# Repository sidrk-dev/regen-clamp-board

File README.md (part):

# Regen clamp + soft-start board (rev F)

**Quick links:** [JLCPCB Ordering & Settings](#ordering-and-cost) · [Manufacturing Files (`jlcpcb/`)](jlcpcb/) · [Schematic PDF](docs/regen_precharge_schematic.pdf) · [Factory Assembly View](docs/regen_precharge_revF_factory.png) · [Bring-up](#bring-up)

**Prototype for bench evaluation.** The board has not been built or measured. KiCad ERC and DRC pass on this copy,
and the control rail and braking figures below are design targets from calculation and simulation.

**Brake capacity.** The brake can absorb at most (supply + trip) ÷ R. With one 2 Ω resistor at 36 V and a +4 V trip
that is 20 A of current returned by the motors, net of what the other joints draw. Above that the bus keeps
rising: in simulation a 22 A, 15 ms return reaches 44.2 V, past the moteus r4's 44 V absolute maximum, and 27 A
reaches 53.8 V. Either limit the arm's deceleration and backdriving so the net returned current stays under
about 18 A at 36 V, or fit two resistors in parallel (see [Two brake resistors](#two-brake-resistors-in-parallel)).
Measure the returned current, resistor duty and connector fit before fast or backdriven operation. The
[engineering review](docs/arm-manufacturing-review.md) has the sweep, the assembly files checked and the
release gates.

A 125 × 100 mm two-layer board that sits between a bench supply and the arm.
The supply plugs into an XT60 in the middle of the left edge; five XT30
outputs sit along the right edge. Outputs 1–3 feed the arm's IM6014 motors, two or
three daisy-chained on each; output 4 feeds the gripper's moteus controller and
output 5 is a spare. It works from 24 V to 48 V supplies, with the brake threshold
set by RV1. A #8-32 mounting hole sits in each corner. It does two jobs:

1. **Regen clamp.** An ideal diode stops motor regeneration from flowing back
   into the supply. When braking pushes the motor bus a set amount above the
   supply, two MOSFETs dump the energy into an external brake resistor. A red
   LED stretches the brake indication by roughly 0.3 s under the simulated conditions.
2. **Soft start (precharge).** The output turns on at about 140 V/s, to reduce inrush when enabling a discharged output. It does not prevent
   sparks when connecting a load to an already charged output bus.

Design inspiration: the [ODrive Regen Clamp](https://docs.odriverobotics.com/v/latest/hardware/regen-clamp-datasheet.html)
(ideal diode plus a brake chopper whose threshold is relative to the input) and
the [mjbots mjpower-ss](https://github.com/mjbots/power_dist/tree/main/hw/mjpower-ss)
(a high-side FET ramped slowly to precharge the load, with an output on/off switch).

## Board renders

| Power input and brake connector | Motor outputs and brake connector |
| --- | --- |
|  |  |
| **Power-input side, opposite corner** | **Motor-output side, opposite corner** |
|  |  |

## Revisions

None of these has been ordered.

Rev F started as a cost-down of rev E. Later rev F edits adjusted the top-layer copper clearances described below.

- **Ordered in 1 oz copper instead of 2 oz.** JLC's live quote on 2026-11-11 for five 125 × 100 mm boards was
  $47.40 in 2 oz and $10.10 in 1 oz. A sheet-resistance and heat calculation from the board file
  (`review_tools/copper_check.py`, see Current handling) gives 3.1 mΩ and 2.2 W of copper heat at 27 A in 1 oz,
  against 1.5 mΩ and 1.1 W in 2 oz; the hottest spot, a MOSFET tab, is calculated at about 65 K above ambient in
  still air against 46 K. The layout still meets JLC's 2 oz rules, so the same Gerbers can be ordered in 2 oz
  if you want that margin back.
- **SW1 is hand-soldered**, which drops one extended-part fee ($3.07). The front stencil now omits its pads and the other hand-solder positions.
- **D12 is a BZT52C16** (C19077413, 15.2–16.8 V) instead of a BZT52C15, same SOD-123 footprint. JLC's catalogue data
  lists it as a Preferred part, with no loading fee on Economic assembly; JLC's part page only says Extended, so check the
  fee on the order page. The fault limit on the control rail rises from about 15 V to under 17 V, still below the
  20 V limits of U4 and the MOSFET gates.
- **Silkscreen:** connector outlines are trimmed 0.25 mm inside the board edge and the MOSFETs' small pin-1 dot is
  gone (Q9's sat on C13's pad; the heavy mark beside pin 1 stays). DRC now reports no warnings at any severity and
  the gate waives nothing. The project footprint library holds the same edits.
- **BUS_ADC** is the new name of the VBUS_ADC telemetry net. Konnect's design review took the old name for a power
  rail and asked for a 10 µF capacitor on it; it now reports no findings.
- The back legend reads rev F, 27 A max, 1 oz Cu, and has a line with the 36 V and 48 V settings.
- **From an independent review of the public rev E files (15 Nov 2026).** It found no netlist, pin, copper or
  fab-file error. Of its four layout points, two were already fixed here (SW1's direction, J5's slot pads) and two
  still held and are fixed now:
  - *Bus-voltage pads were 0.40 mm from ground copper*; IPC-2221B gives 0.5 mm for uncoated terminations at 51–100 V,
    which the bus reaches during braking on a 48 V supply. Every pad on a net that can pass 50 V is now at least
    0.5 mm from ground copper, and the hand-soldered bus pins of the XT connectors and electrolytics 1.0 mm.
    `review_tools/bus_clearance_check.py` shows 29 pads under 0.5 mm before and none after. Raising the whole top
    ground pour to 0.5 mm was tried first and rejected: it cut the ground of U4 and C19.
  - *The back legend ended 0.08 mm from the board edge*; it is moved 5 mm right. KiCad's DRC only reports
    silkscreen that crosses the edge, so `review_tools/silk_edge_check.py` now checks the margin.
  - *48 V margin*: the limit at 48 V is now +5 V (TP9 at most 7.7 V) instead of +6 V, as the review recommends (this also keeps `U3A`'s inputs below the `LM393` cold `VCC − 2.0 V` common-mode ceiling up to 55 V).
  - `tools/review_tools/check_bom.py` now checks capacitor voltage ratings, electrolytic can dimensions, and `>= 75 V` (`>= 150 V` on `R6, R36`) working-voltage ratings on bus-connected resistors against the catalogue.
  - *0.1 % sense resistors*, added 16 Nov because the board will also run on 48 V: R10 and R14 are now 100 k 0.1 %
    (Yageo RT0603BRD07100KL, C122538) and R11 and R15 20 k 0.1 % (RT0603BRD0720KL, C723637), same 0603 footprint,
    75 V rated. The review puts the trip spread at 48 V at about 0.6 V with them, against 3.5 V with 1 % parts, so the
    brake releases above the supply in every corner and the interlock is a backup. Both values remain on the
    machine BOM as Extended parts. The tolerance figures elsewhere in this file (±1.4 V at 36 V, ±1.8 V at 48 V) are the
    older 1 % numbers and are now pessimistic. `build-scripts/sense_resistors.py` is the record.
  `build-scripts/review_nov15.py` is the record of the board edits.
- **SW1 is labelled OFF and ON at the two ends of its travel**, in place of one "ON/OFF" caption. The MSK12C02
  drawing shows the knob at the pin-3 end joining pins 3 and 2, and at the pin-1 end joining 2 and 1. Pin 1 is ground
  and pin 2 is EN, so ON is the slider toward the bottom board edge. `tools/check_parts.py` now fails if the labels are swapped.
- **Connector polarity settled from the Amass drawings**, and checked by `tools/check_parts.py`: pad 2 of J1 and of
  J2–J4, J6, J7 is the contact at the flat end of the housing, which is the + contact (see Verification status).
- New simulations: `sim_post_layout.cir`, `sim_soft_start.cir`, and `tools/review_tools/full_board_spice_check.py` (see Verification status).
- **The six TO-263 MOSFETs (`Q1, Q2, Q3, Q7, Q8, Q9`) stay on JLCPCB's SMT reflow line**, while the 1206 capacitors
  (`C1, C2, C6`) remain hand-soldered (reflow them with hot air or a hot plate rather than a point iron,
  to avoid ceramic thermal-shock cracks). The MOSFETs retain the corrected 3D model offset and front stencil paste openings.
- **R6, the SMC and SMA diodes (D1, D2, D4, D7), the two SOD-123 Zeners (D11, D12) and the SOT-223 transistor
  (Q4) stay machine-placed.** An earlier commit on this branch moved them to hand soldering; only D11 carried a fee,
  so the other seven added hand work for no saving, and the owner asked for them to go back on the machine.
  The schematic's assembly field and the PCB placement exclusions drive the exports.
- **From a follow-up review (17–18 Nov 2026):** `J1` and `J5` contact holes are centred in Amass's `2.90 +0.10/-0.00 mm`
  and `0.80 +0.10/-0.00 × 1.90 +0.10/-0.00 mm` windows at **3.0 mm** with **0.9 × 2.0 mm** fixing slots (`1.5 × 2.6 mm`
  pads, keeping the `0.30 mm` plated ring) so JLCPCB's `-0.08 mm` plating tolerance cannot finish undersize; thermal relief
  spokes now protect the five 470 µF bulk capacitors (`C7, C8, C15, C16, C17`), `J12` pin 1, the hand-soldered SMDs
  (`C1, C2, C6, SW1`), and 58 small `0603`/`0805`/`SOD` passives (preventing reflow tombstoning and `SW1` housing heat
  damage while keeping MOSFET, power-diode, and XT connector pads solid); `C8`'s silkscreen label moved clear of `D2`'s
  body; `tools/sch_layout.py` is bundled in `tools/`; `B.Paste` is included in the 11-file Gerber archive; and the schematic
  title block and notes are updated to rev F, 27 A, four output bulk capacitors and D12 under 17 V (`tools/rev_f_review_fixes.py`).
- The PCB and schematic both use the bundled 1 mm fiducial footprint so that a change in the installed KiCad library does not affect the release checks.
- `build-scripts/cost_down.py` and `tools/rev_f_review_fixes.py` are the record of these edits.

Rev E, changes from rev D. Most of these were found by independent reviews:

- **U2 CJ431 pins corrected.** The board used TL431 numbering, but this part's SOT-23
  is pin 1 REF, pin 2 K, pin 3 A. The control rail could not have worked.
- **RV1 ends swapped**, so clockwise raises the brake threshold.
- **J1 and J5 holes enlarged** to 2.9 mm with 0.8 × 1.9 mm fixing slots, per the
  XT60PW-M30 drawing served for C98732. The old 2.7 mm holes and 0.6 × 1.7 mm slots
  could not take the connector. The XT60PW-F PDF gives no PCB holes, so J5 uses the
  same sizes.
- **C13 moved out from under Q9, and R30–R33 moved clear of the MOSFET plastic.**
  C13 sat under Q9's body and gate lead, which would have stopped assembly. A DRC
  warning showed it, and it had been wrongly waived as cosmetic.
- **Ideas from a friend's board:** a UCC27517 gate driver (U4) replaces the Q5/Q6 transistor pair, so
  the brake switches in tens of nanoseconds and the LM393 no longer sinks a transistor's base current;
  the five 470 µF capacitors (four on the output, one on the input) are now 100 V (12.5 × 30 mm, same footprint, 5 mm taller); and J12 gives a
  microcontroller GND, BUS_ADC (VOUT × 0.053, 3.3 V at 62 V) and BRK_FLAG (open drain, low while braking).
- **Q4 is now a BCP56-16 in SOT-223** (94 °C/W, 1.33 W) instead of an MMBT5551 in SOT-23 (416 °C/W).
  Braking adds rail load, and the old part could pass 150 °C at moderate ambient. It sits at the lower left.
- **J5's fixing pads give a 0.3 mm plated ring** on every side, for JLC's 2 oz rule; J5 moved 0.4 mm inboard.
- **Copper kept out of an 11.5 mm circle round each corner hole**, both layers, so a
  metal screw head or washer can't short VIN or VOUT to a grounded standoff.
- **D10 (1N4148WS) added across Q4's base and emitter.** When VOUT collapses while C9
  still holds the rail up, the junction no longer breaks down in reverse.
- **D11 (BZT52C12, 12 V) clamps HGATE to VOUT.** The 400 nF soft-start capacitor holds
  HGATE up when VOUT falls, and with no clamp HGATE minus OUT could pass U1's 15 V
  absolute maximum and the MOSFETs' 20 V gate limit: 18 V or more after long regen, far
  more on a supply removal or output short. R5 limits the peak clamp current to ~47–60 mA (`< 0.3 mJ`).
  Scope HGATE minus OUT at bring-up.
- **D12 (BZT52C15) clamps Q4's base.** If U2 or R7 opens, R6 would pull the rail up to the bus,
  past the LM393's 36 V and the brake MOSFETs' 20 V gate limit. Now the rail stays under about 15 V.
- **Five XT30 outputs instead of three**, so the arm's seven motors split two or three per
  output, all within the XT30's 15 A rating.
- **C3 raised to 470 nF**, from TI's VCAP ≥ 10 × (Ciss Q1 + Ciss Q2) with four MOSFETs.
- **C17 (470 µF 100 V) added on VIN.** Only 1 µF sat there, so turning Q2/Q8 off under load
  could spike VIN past U1's 70 V through the supply lead's inductance. Connect the supply with it off.
- **J2–J5 moved out** so each connector's nose hangs off the board edge. The mating plug's
  shell wraps the nose and could have hit the PCB and stopped short of full mating.
- **D1 and D2 ground returns strengthened** from one via to three.
- **U1's exposed pad paste reduced to about 82 %** (0.08 mm smaller each side), per TI's stencil example.
- **From the final three-model review:** R40 (100 k) limits current into U3 pin 6 if the rail drops
  while C12 is charged; R41 (10 k) in Q10's base limits a reversed-supply fault path through Q10/Q11;
  C18 (1 nF) filters noise from the J11 wiring on CMP_OUT; C19 (1 µF) is a local supply for the
  brake gate driver (Q5/Q6 then, U4 now); C3 is now 1 µF so it stays above TI's 271 nF after DC-bias loss; C13 moved
  0.4 mm further from Q9's gate pad; connector fixing pads enlarged for 2 oz plating; the screw
  keep-out widened so no copper sits within 5.5 mm of a hole centre.

Rev D, changes from rev C:

- XT60 input centred on the left edge and the three XT30 outputs centred on the
  right edge, so the four corners are free for #8-32 holes (4.5 mm, 5 mm in from
  each edge).
- Two debug LEDs: D8 (white, SUPPLY) shows the PSU is connected even with SW1
  off; D9 (yellow, THERM OPEN) shows, while the output bus is up, that the J11
  thermal loop is open, which is the usual reason the brake never fires.
- Eight more test points (TP18–TP25): OV, CDVDT, interlock, second brake gate,
  thermal loop, driver output, and two more GND holes by the input and outputs.
- The VIN pour now fills the area beside U1, which keeps input current density
  down with the XT60 in its new place.
- Design rules raised to JLCPCB's 2-layer 2 oz limits, 0.16 mm track and
  clearance (earlier revisions used 1 oz limits, 0.127/0.15 mm, and 51 tracks
  were too thin for 2 oz). The 2 oz stackup is now recorded in the board file.
- Three fiducials added, and the router's dead-end stubs removed.

Rev C, changes from rev B:

- XT60 input instead of XT90, and 3 outputs instead of 7.
- Brake interlock (Q10, Q11): the brake is intended to be held off while the ideal diode
  conducts. The behavioral latch test covers one tolerance corner; it does not
  prove that every transient and component fault avoids supply-fed braking. In rev B, worst-case
  1 % resistor tolerances at the lowest trim setting could put the brake's
  release point below the supply at 36–48 V, and the brake would then latch on
  and pass about 24 A from the PSU into the resistor.
- One 10 Ω gate resistor per paralleled MOSFET (R30–R33), to stop parasitic
  oscillation while the soft-start pair runs in its linear region.
- Gate drive nets run on the top layer between the power pours, so no gate
  traces cut the bottom ground plane.
- R26 470 Ω (was 1 kΩ): the intended emitter follower has more collector headroom. The
  earlier claim of a guaranteed 11.3 V rail at 15 V is withdrawn; CJ431 bias
  current and the exact U2 pinout must be corrected.
- TVS diodes D1/D2 use JLC's Preferred SMCJ51A (C42371549): same part, no
  extended-part fee.

## Ratings

These are board design targets. Each attached controller must tolerate the maximum
bus voltage, including regen and transients. Unitree's public N6014B-12.6 page
lists 24–75 V input, so 15 V is outside that motor's published range. Moteus
limits depend on the exact model: r4 is 44 V absolute maximum, c1 is 51 V,
and n1/x1 are 54 V. A generic "moteus" output is not validated for 48 V plus regen.
See the manufacturer [Unitree specification](https://www.unitree.com/IM6014/)
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
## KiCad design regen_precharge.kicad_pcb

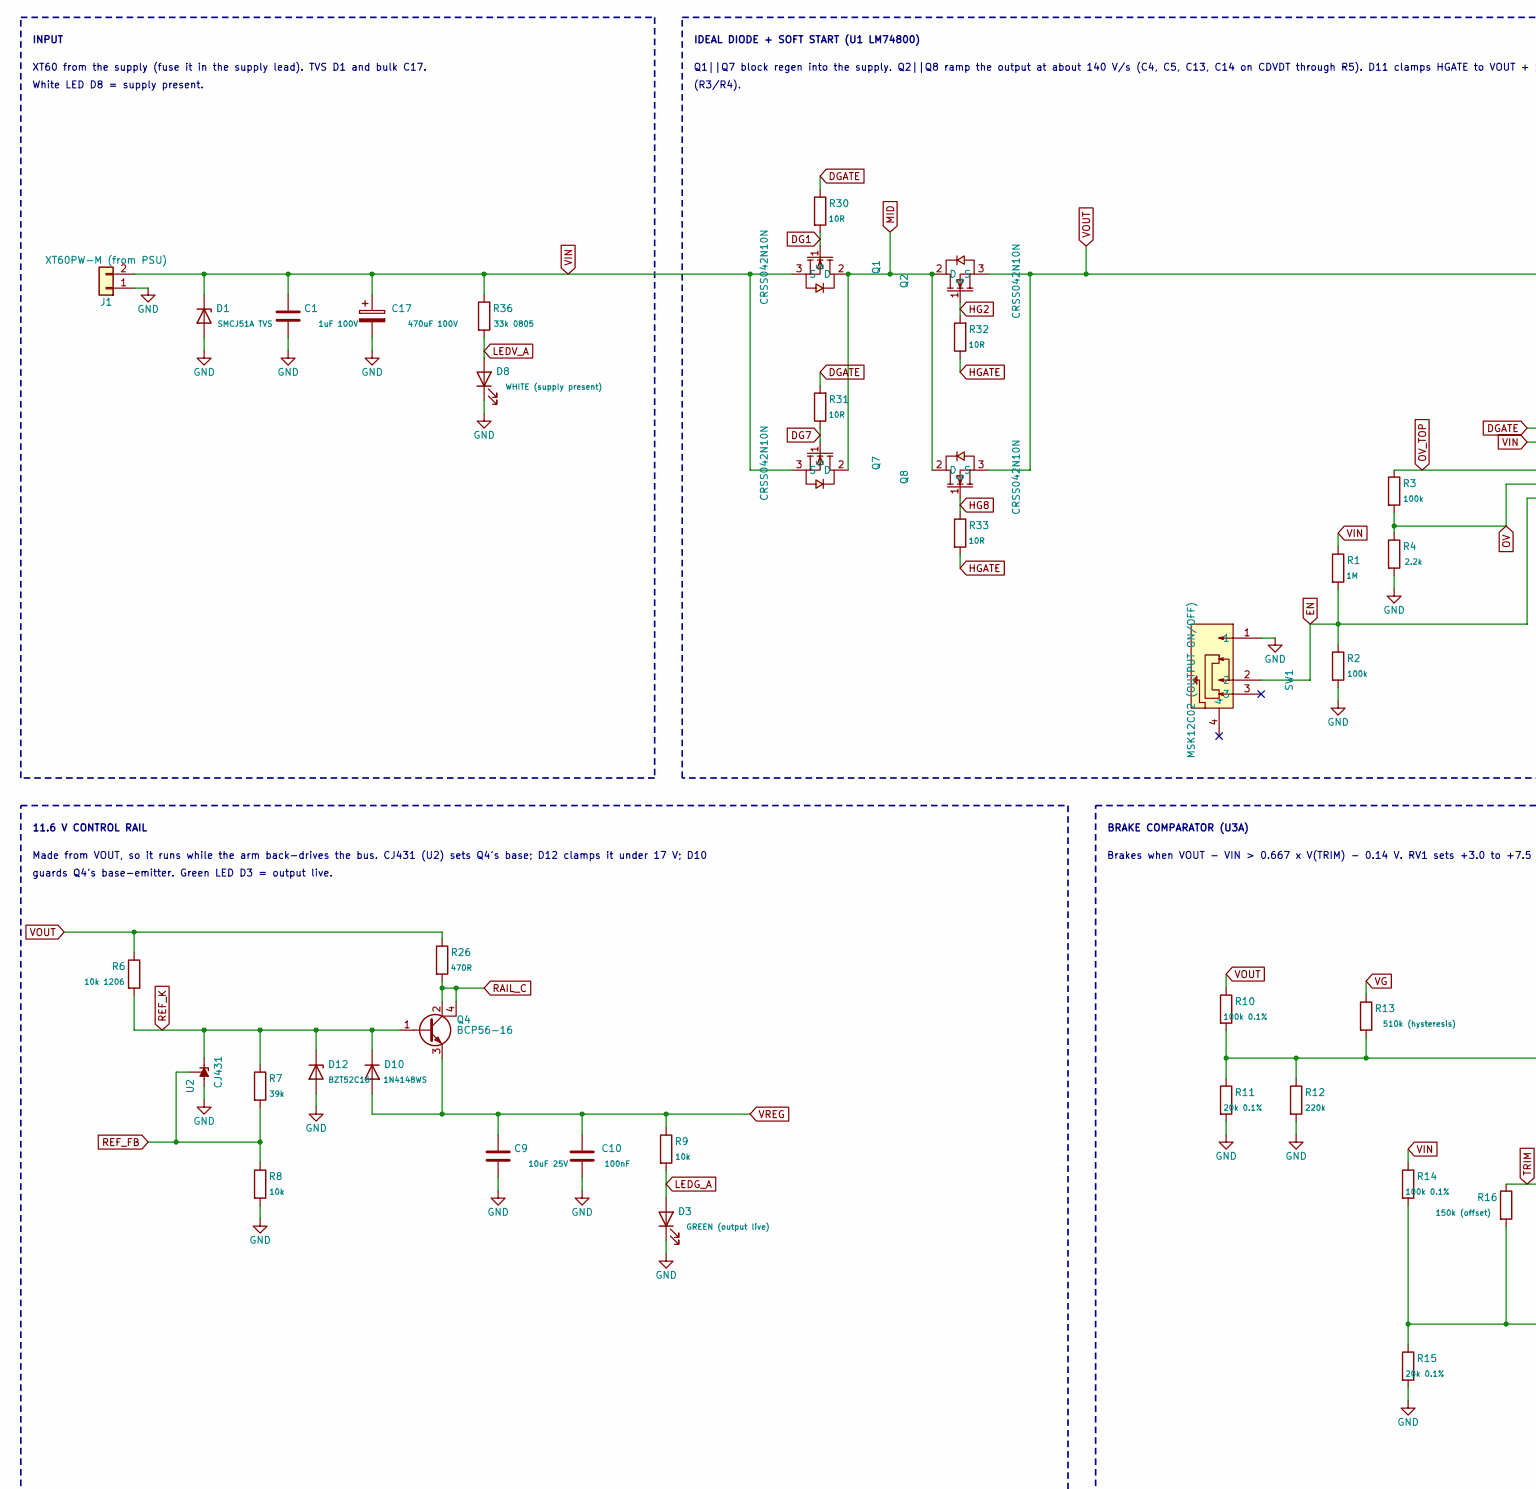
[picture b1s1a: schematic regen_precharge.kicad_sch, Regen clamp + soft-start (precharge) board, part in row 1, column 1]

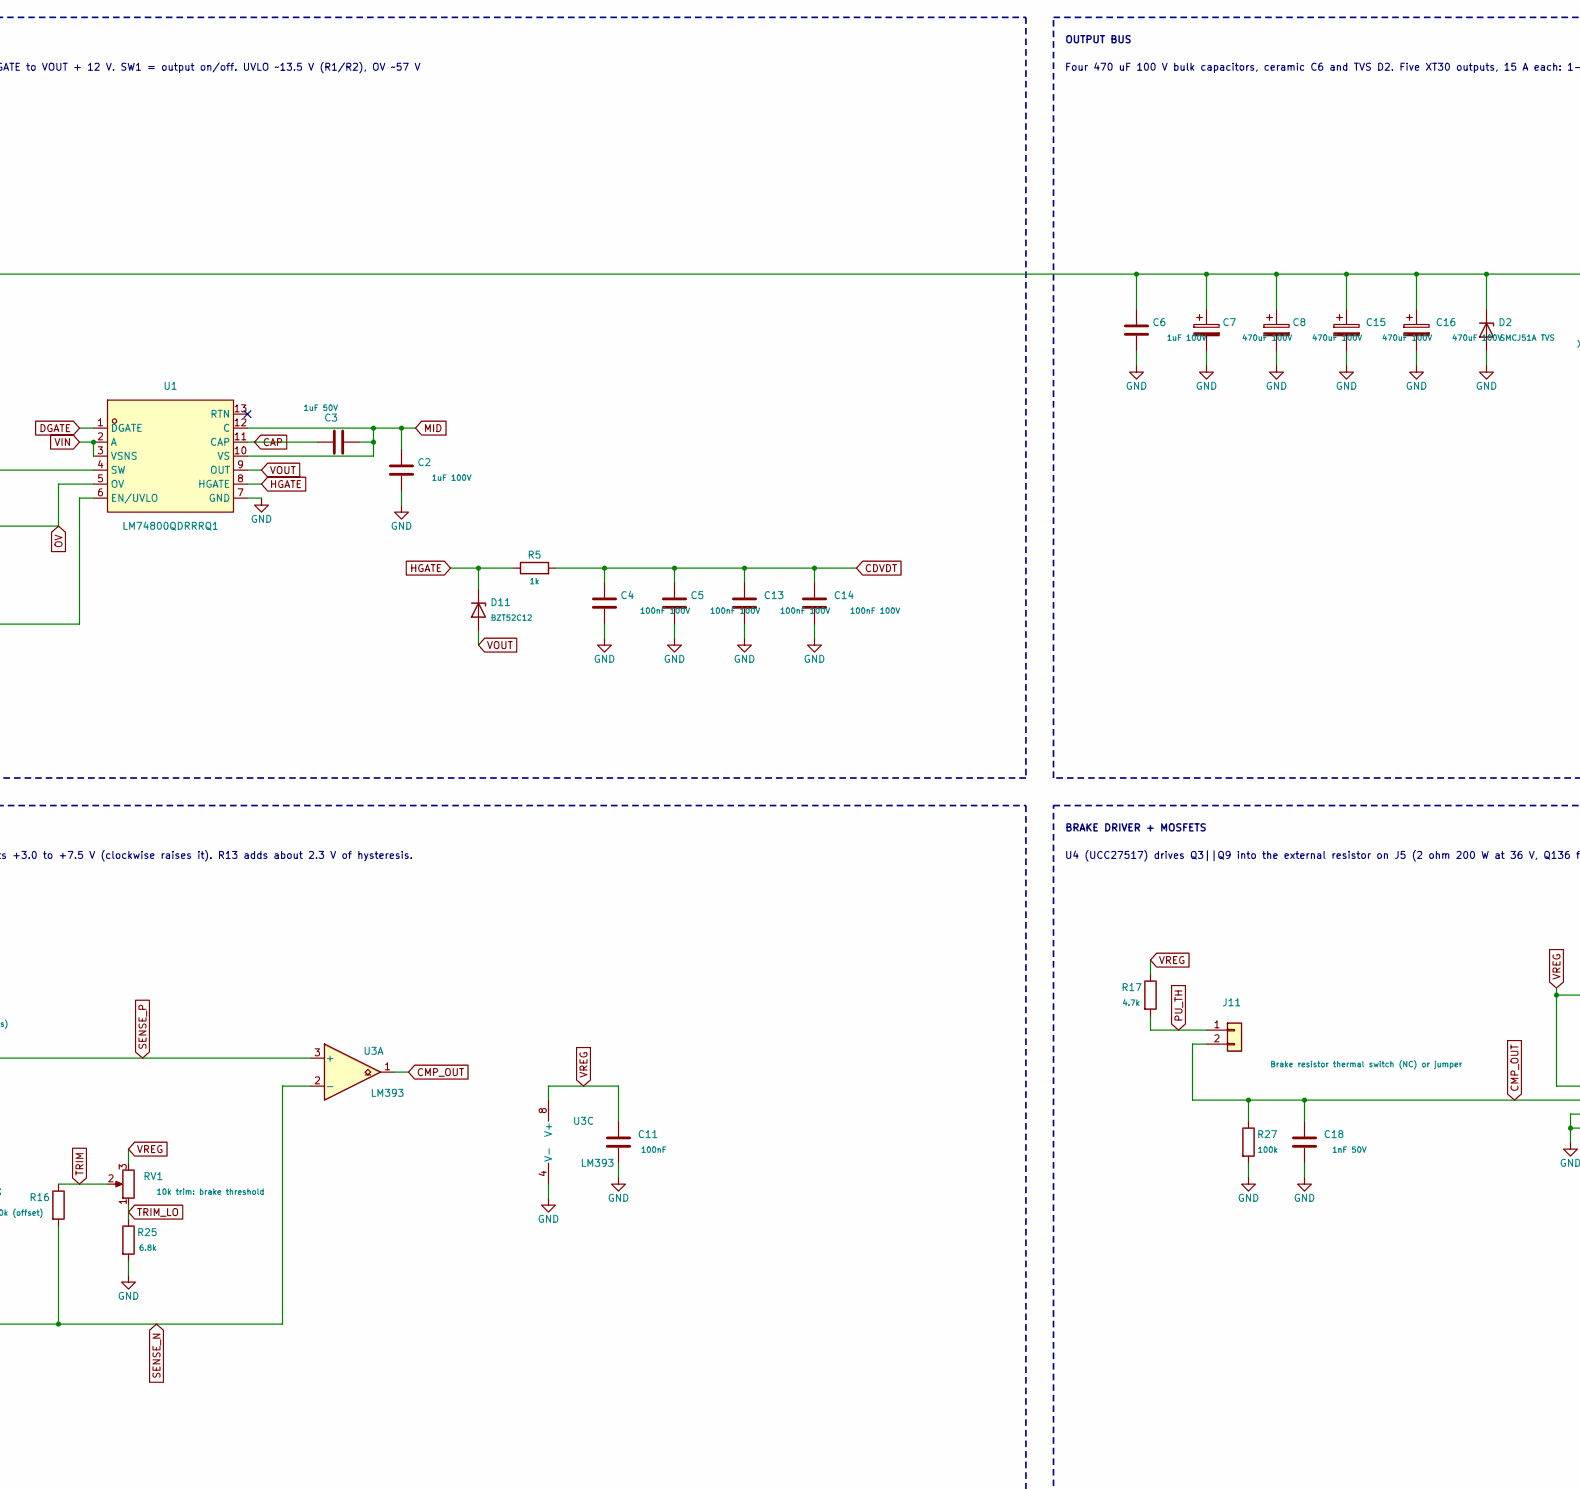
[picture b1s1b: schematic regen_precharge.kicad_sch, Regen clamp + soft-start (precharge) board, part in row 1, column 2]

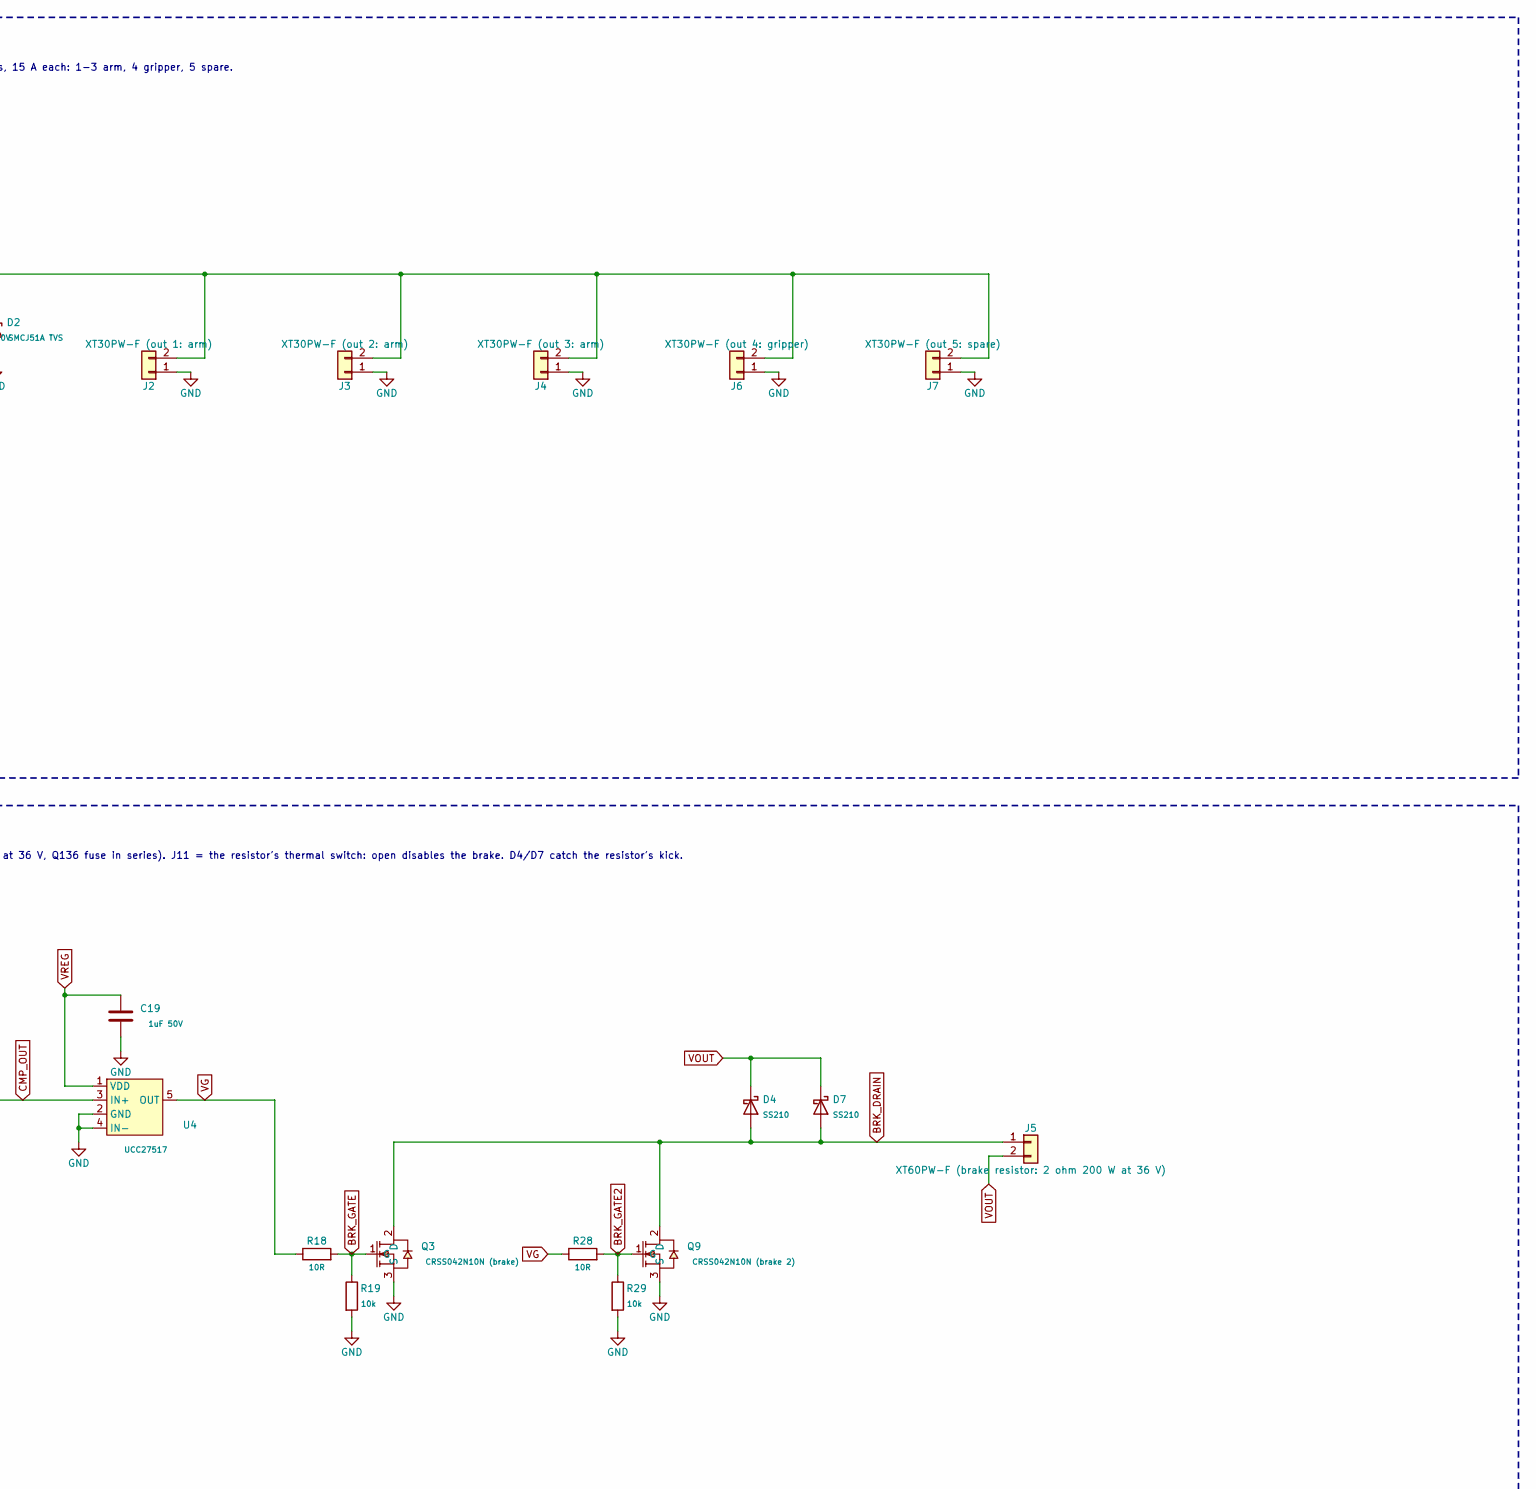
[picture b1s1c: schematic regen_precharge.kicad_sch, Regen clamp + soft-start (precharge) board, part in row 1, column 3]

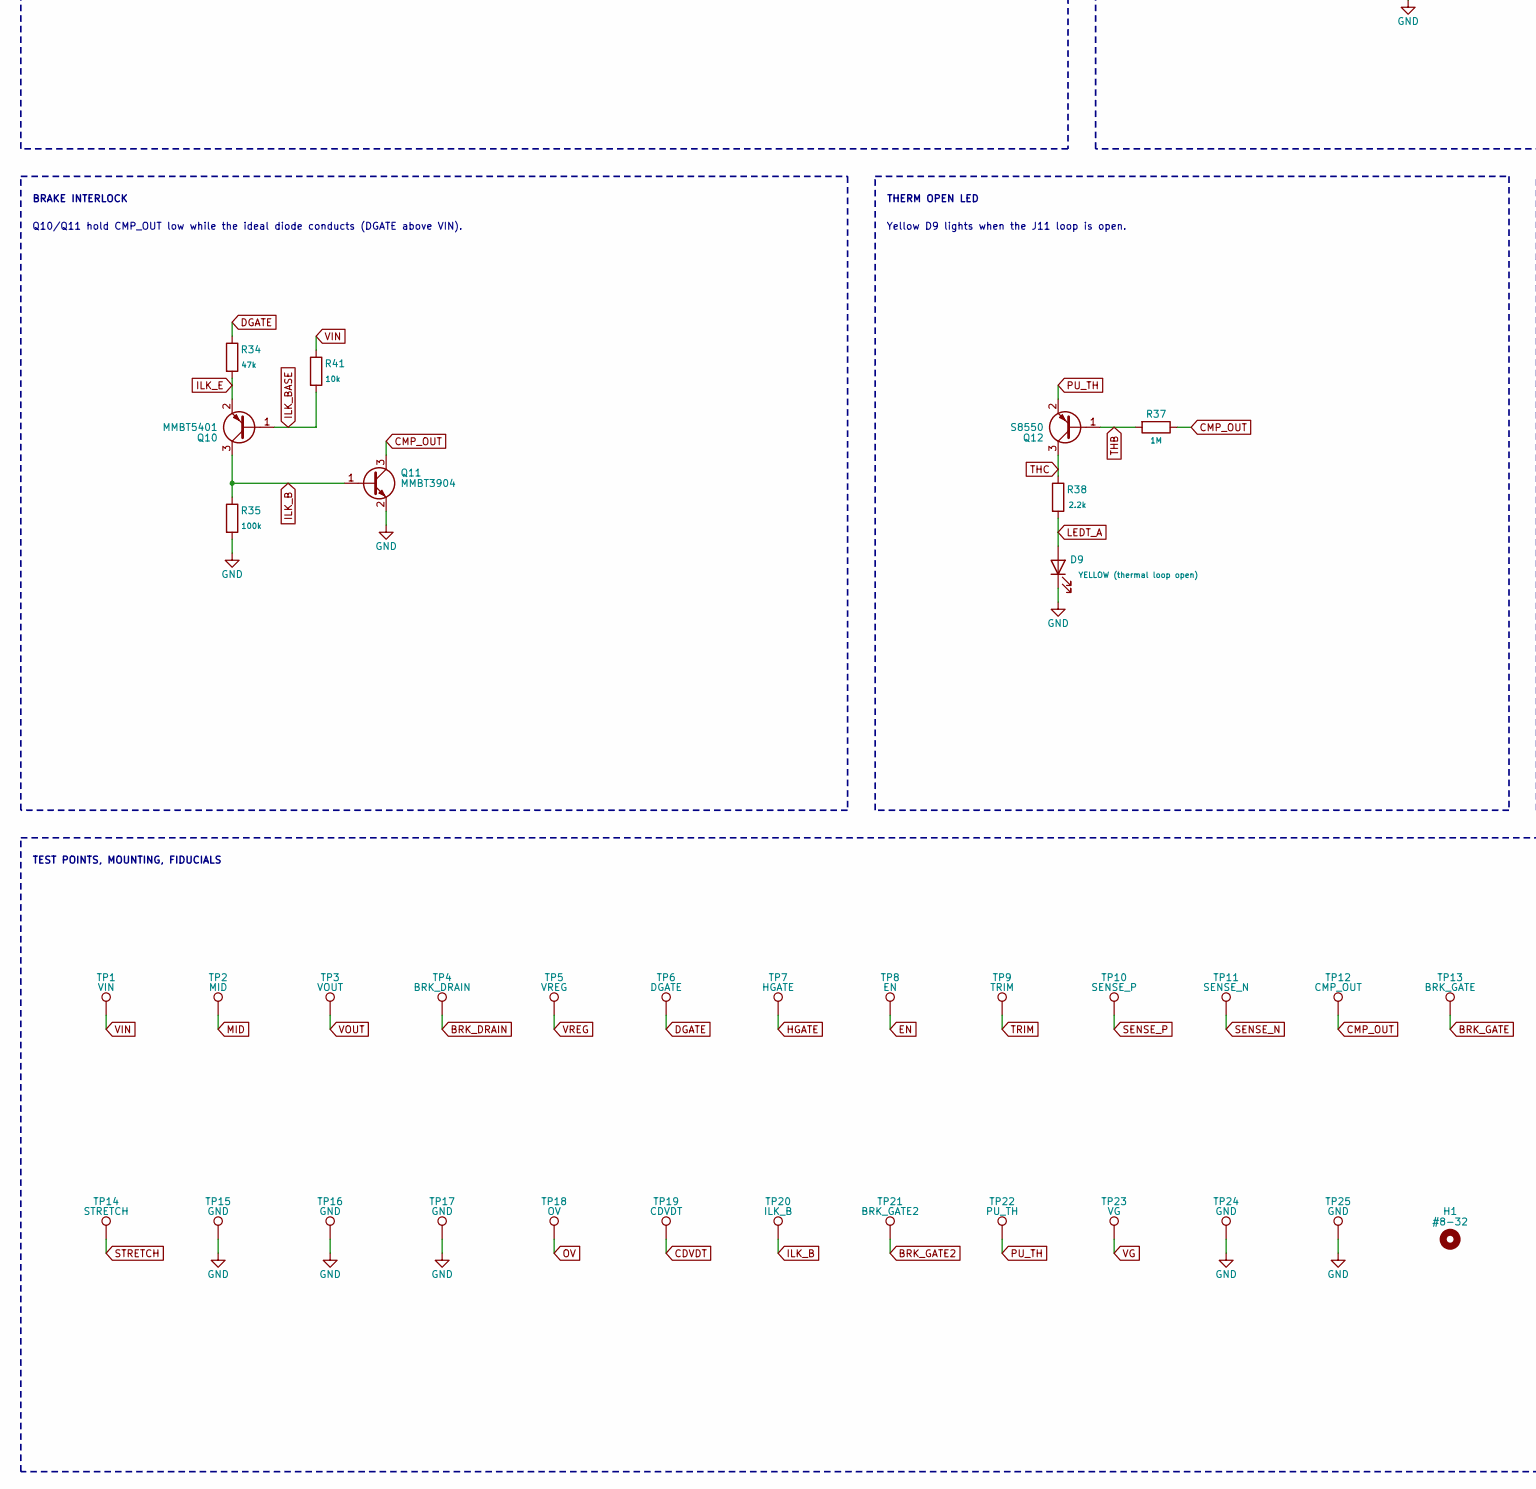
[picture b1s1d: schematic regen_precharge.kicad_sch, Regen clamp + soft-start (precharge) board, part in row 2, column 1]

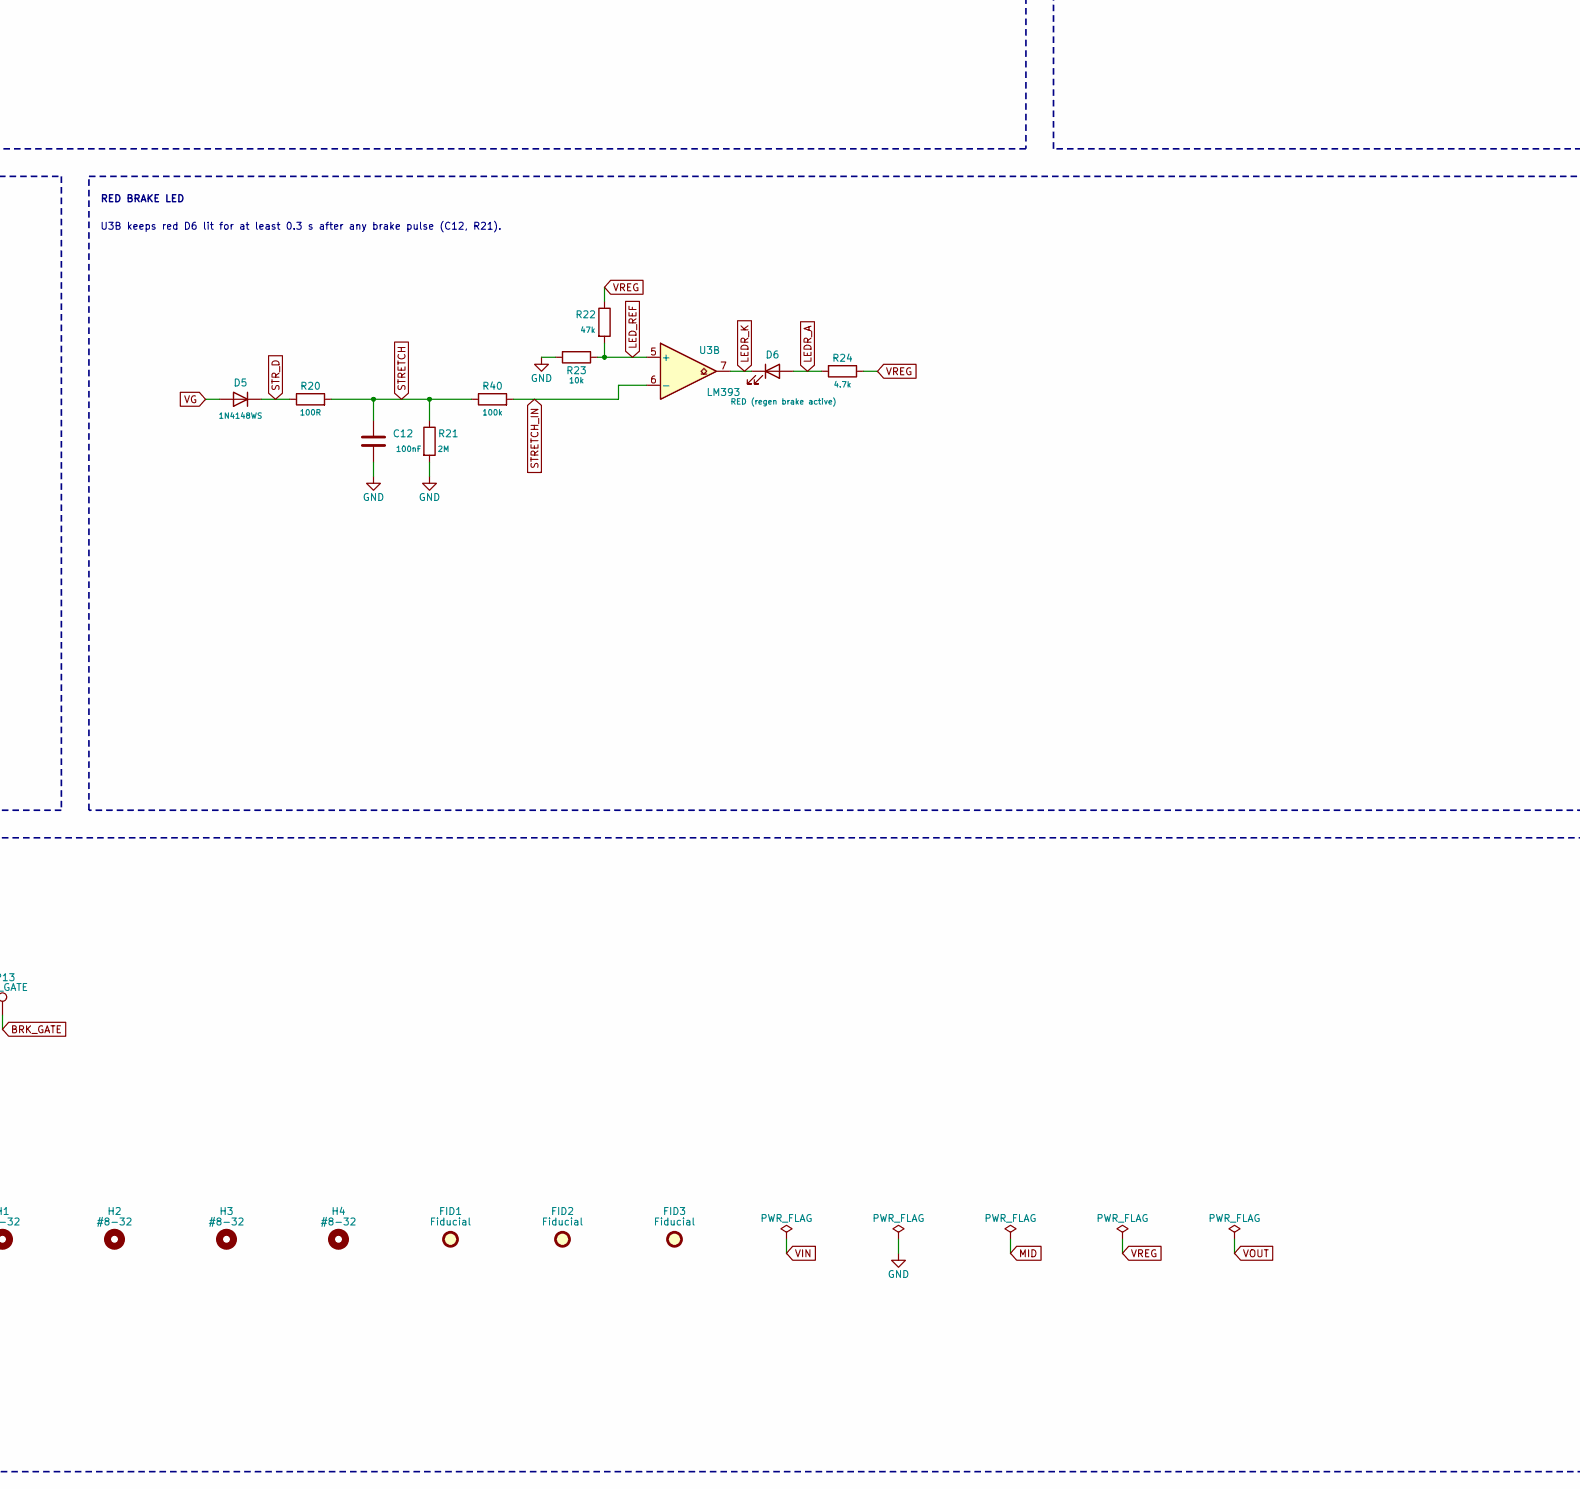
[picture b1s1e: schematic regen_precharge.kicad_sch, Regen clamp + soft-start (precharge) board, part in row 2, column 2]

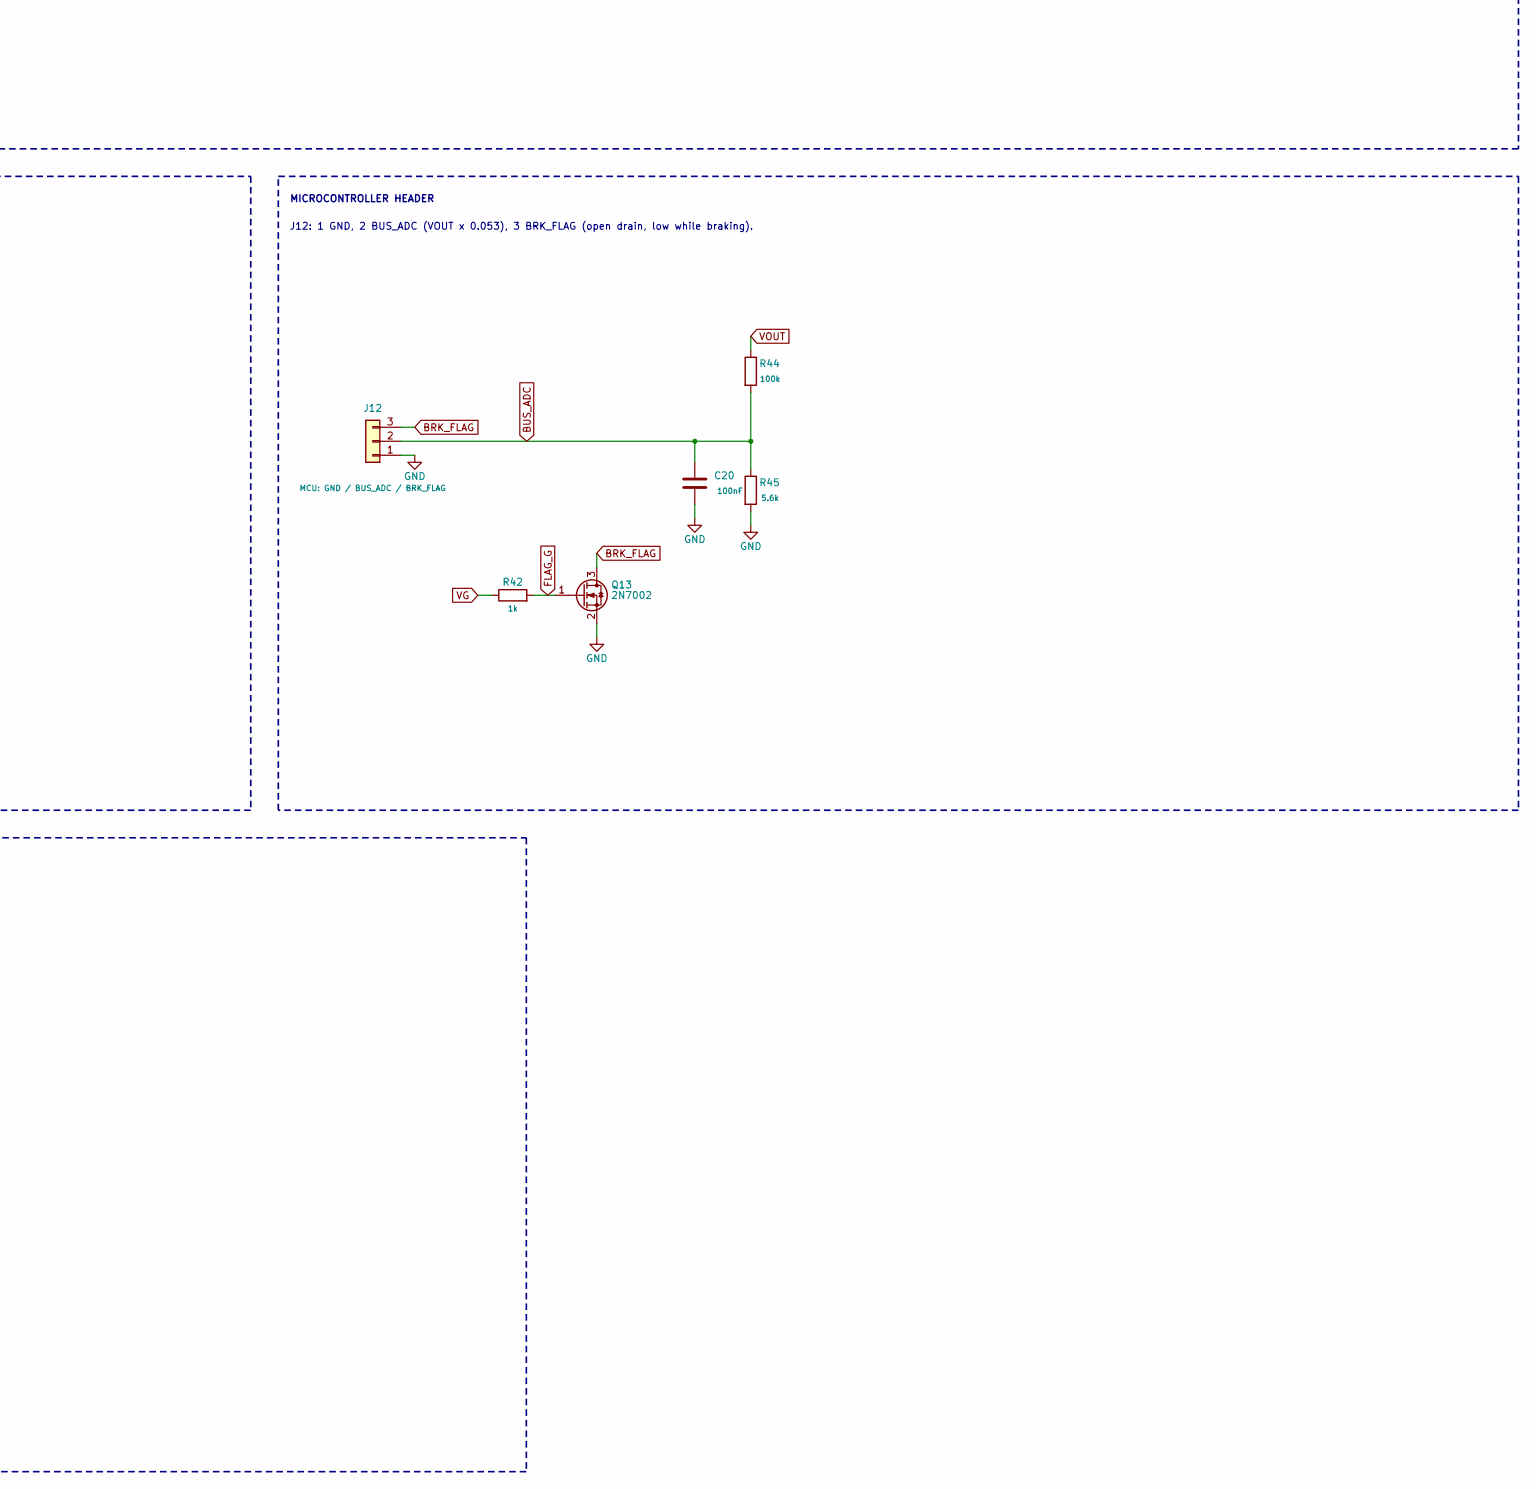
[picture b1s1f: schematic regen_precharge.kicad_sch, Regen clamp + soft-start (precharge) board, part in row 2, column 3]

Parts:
C1, C2, C6: 1uF 100V; C_1206_3216Metric; LCSC C13832
C3, C19: 1uF 50V; C_0603_1608Metric; LCSC C15849
C4, C5, C13, C14: 100nF 100V; C_0805_2012Metric; LCSC C28233
C7, C8, C15, C16, C17: 470uF 100V; CP_Radial_D12.5mm_P5.00mm; LCSC C443159
C9: 10uF 25V; C_0805_2012Metric; LCSC C15850
C10, C11, C12, C20: 100nF; C_0603_1608Metric; LCSC C14663
C18: 1nF 50V; C_0603_1608Metric; LCSC C1588
D1, D2: SMCJ51A TVS; D_SMC; LCSC C42371549
D3: GREEN (output live); LED_0805_2012Metric; LCSC C2297
D4, D7: SS210; D_SMA; LCSC C14996
D5, D10: 1N4148WS; D_SOD-323; LCSC C2128
D6: RED (regen brake active); LED_0603_1608Metric; LCSC C2286
D8: WHITE (supply present); LED_0603_1608Metric; LCSC C2290
D9: YELLOW (thermal loop open); LED_0805_2012Metric; LCSC C2296
D11: BZT52C12; D_SOD-123; LCSC C2932744
D12: BZT52C16; D_SOD-123; LCSC C19077413
FID1, FID2, FID3: Fiducial; Fiducial_1mm_Mask2mm
H1, H2, H3, H4: #8-32; MountingHole_4.5mm
J1: XT60PW-M (from PSU); AMASS_XT60PW-M30_1x02_P7.20mm_Horizontal; LCSC C98732
J2: XT30PW-F (out 1: arm); AMASS_XT30PW-F_1x02_P2.50mm_Horizontal_pegs; LCSC C2913282
J3: XT30PW-F (out 2: arm); AMASS_XT30PW-F_1x02_P2.50mm_Horizontal_pegs; LCSC C2913282
J4: XT30PW-F (out 3: arm); AMASS_XT30PW-F_1x02_P2.50mm_Horizontal_pegs; LCSC C2913282
J5: XT60PW-F (brake resistor: 2 ohm 200 W at 36 V); AMASS_XT60PW-F_1x02_P7.20mm_Horizontal_2.9mm; LCSC C428722
J6: XT30PW-F (out 4: gripper); AMASS_XT30PW-F_1x02_P2.50mm_Horizontal_pegs; LCSC C2913282
J7: XT30PW-F (out 5: spare); AMASS_XT30PW-F_1x02_P2.50mm_Horizontal_pegs; LCSC C2913282
J11: Brake resistor thermal switch (NC) or jumper; PinHeader_1x02_P2.54mm_Vertical; LCSC C492401
J12: MCU: GND / BUS_ADC / BRK_FLAG; PinHeader_1x03_P2.54mm_Vertical; LCSC C2937625
Q1, Q2, Q7, Q8: CRSS042N10N; TO-263-3_L10.2-W10.7-P5.08-LS16.2-TL; LCSC C410926
Q3: CRSS042N10N (brake); TO-263-3_L10.2-W10.7-P5.08-LS16.2-TL; LCSC C410926
Q4: BCP56-16; SOT-223; LCSC C41375109
Q9: CRSS042N10N (brake 2); TO-263-3_L10.2-W10.7-P5.08-LS16.2-TL; LCSC C410926
Q10: MMBT5401; SOT-23; LCSC C8326
Q11: MMBT3904; SOT-23; LCSC C20526
Q12: S8550; SOT-23; LCSC C105432
Q13: 2N7002; SOT-23; LCSC C8545
R1, R37: 1M; R_0603_1608Metric; LCSC C22935
R2, R3, R27, R35, R40, R44: 100k; R_0603_1608Metric; LCSC C25803
R4, R38: 2.2k; R_0603_1608Metric; LCSC C4190
R5, R42: 1k; R_0603_1608Metric; LCSC C21190
R6: 10k 1206; R_1206_3216Metric; LCSC C17902
R7: 39k; R_0603_1608Metric; LCSC C23153
R8, R9, R19, R23, R29, R41: 10k; R_0603_1608Metric; LCSC C25804
R10, R14: 100k 0.1%; R_0603_1608Metric; LCSC C122538
R11, R15: 20k 0.1%; R_0603_1608Metric; LCSC C723637
R12: 220k; R_0603_1608Metric; LCSC C22961
R13: 510k (hysteresis); R_0603_1608Metric; LCSC C23192
R16: 150k (offset); R_0603_1608Metric; LCSC C22807
R17, R24: 4.7k; R_0603_1608Metric; LCSC C23162
R18, R28, R30, R31, R32, R33: 10R; R_0603_1608Metric; LCSC C22859
R20: 100R; R_0603_1608Metric; LCSC C22775
R21: 2M; R_0603_1608Metric; LCSC C22976
R22, R34: 47k; R_0603_1608Metric; LCSC C25819
R25: 6.8k; R_0603_1608Metric; LCSC C23212
R26: 470R; R_0603_1608Metric; LCSC C23179
R36: 33k 0805; R_0805_2012Metric; LCSC C17633
R45: 5.6k; R_0603_1608Metric; LCSC C23189
RV1: 10k trim: brake threshold; RES-ADJ-TH_3362P; LCSC C58159
SW1: MSK12C02 (OUTPUT ON/OFF); SW-TH_MSK12C02; LCSC C431540
TP1: VIN; TestPoint_Pad_D1.5mm
TP2: MID; TestPoint_Pad_D1.5mm
TP3: VOUT; TestPoint_Pad_D1.5mm
TP4: BRK_DRAIN; TestPoint_Pad_D1.5mm
TP5: VREG; TestPoint_Pad_D1.5mm
TP6: DGATE; TestPoint_Pad_D1.5mm
TP7: HGATE; TestPoint_Pad_D1.5mm
TP8: EN; TestPoint_Pad_D1.5mm
TP9: TRIM; TestPoint_Pad_D1.5mm
TP10: SENSE_P; TestPoint_Pad_D1.5mm
TP11: SENSE_N; TestPoint_Pad_D1.5mm
TP12: CMP_OUT; TestPoint_Pad_D1.5mm
TP13: BRK_GATE; TestPoint_Pad_D1.5mm
TP14: STRETCH; TestPoint_Pad_D1.5mm
TP15, TP16, TP17, TP24, TP25: GND; TestPoint_THTPad_D2.0mm_Drill1.0mm
TP18: OV; TestPoint_Pad_D1.5mm
TP19: CDVDT; TestPoint_Pad_D1.5mm
TP20: ILK_B; TestPoint_Pad_D1.5mm
TP21: BRK_GATE2; TestPoint_Pad_D1.5mm
TP22: PU_TH; TestPoint_Pad_D1.5mm
TP23: VG; TestPoint_Pad_D1.5mm
U1: LM74800QDRRRQ1; WSON-12_L3.0-W3.0-P0.50-TL-EP-2; LCSC C3215600
U2: CJ431; SOT-23; LCSC C3113
U3: LM393; SOIC-8_3.9x4.9mm_P1.27mm; LCSC C7955
U4: UCC27517; SOT-23-5; LCSC C99395

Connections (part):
BRK_DRAIN: D4.2 (A), D7.2 (A), J5.1, Q3.2 (D), Q9.2 (D), TP4.1
BRK_FLAG: J12.3, Q13.3 (D)
BRK_GATE: Q3.1 (G), R18.2, R19.1, TP13.1
BRK_GATE2: Q9.1 (G), R28.2, R29.1, TP21.1
BUS_ADC: C20.1, J12.2, R44.2, R45.1
CAP: C3.1, U1.11 (CAP)
CDVDT: C4.1, C5.1, C13.1, C14.1, R5.2, TP19.1
CMP_OUT: C18.1, J11.2, Q11.3 (C), R27.1, R37.1, TP12.1, U3.1, U4.3 (IN+)
DG1: Q1.1 (G), R30.2
DG7: Q7.1 (G), R31.1
DGATE: R30.1, R31.2, R34.1, TP6.1, U1.1 (DGATE)
EN: R1.2, R2.1, SW1.2, TP8.1, U1.6 (EN/UVLO)
FLAG_G: Q13.1 (G), R42.2
GND: C1.2, C2.2, C4.2, C5.2, C6.2, C7.2, C8.2, C9.2, C10.2, C11.2, C12.2, C13.2, C14.2, C15.2, C16.2, C17.2, C18.2, C19.2, C20.2, D1.2 (A), D2.2 (A), D3.1 (K), D8.1 (K), D9.1 (K), D12.2 (A), J1.1, J2.1, J3.1, J4.1, J6.1, J7.1, J12.1, Q3.3 (S), Q9.3 (S), Q11.2 (E), Q13.2 (S), R2.2, R4.2, R8.2, R11.2, R12.2, R15.2, R19.2, R21.2, R23.2, R25.2, R27.2, R29.2, R35.2, R45.2, SW1.1, TP15.1, TP16.1, TP17.1, TP24.1, TP25.1, U1.7 (GND), U2.3 (A), U3.4 (V-), U4.2 (GND), U4.4 (IN-)
HG2: Q2.1 (G), R32.2
HG8: Q8.1 (G), R33.1
HGATE: D11.1 (K), R5.1, R32.1, R33.2, TP7.1, U1.8 (HGATE)
ILK_B: Q10.3 (C), Q11.1 (B), R35.1, TP20.1
ILK_BASE: Q10.1 (B), R41.2
ILK_E: Q10.2 (E), R34.2
LEDG_A: D3.2 (A), R9.2
LEDR_A: D6.2 (A), R24.2
LEDR_K: D6.1 (K), U3.7
LEDT_A: D9.2 (A), R38.2
LEDV_A: D8.2 (A), R36.2
LED_REF: R22.2, R23.1, U3.5 (+)
MID: C2.1, C3.2, Q1.2 (D), Q2.2 (D), Q7.2 (D), Q8.2 (D), TP2.1, U1.10 (VS), U1.12 (C)
OV: R3.2, R4.1, TP18.1, U1.5 (OV)
OV_TOP: R3.1, U1.4 (SW)
PU_TH: J11.1, Q12.2 (E), R17.2, TP22.1
RAIL_C: Q4.2 (C), Q4.4 (C), R26.2
REF_FB: R7.2, R8.1, U2.1 (REF)
REF_K: D10.1 (K), D12.1 (K), Q4.1 (B), R6.2, R7.1, U2.2 (K)
SENSE_N: R14.2, R15.1, R16.2, TP11.1, U3.2 (-)
SENSE_P: R10.2, R11.1, R12.1, R13.2, TP10.1, U3.3 (+)
STRETCH: C12.1, R20.2, R21.1, R40.1, TP14.1
STRETCH_IN: R40.2, U3.6 (-)
STR_D: D5.1 (K), R20.1
THB: Q12.1 (B), R37.2
THC: Q12.3 (C), R38.1
TRIM: R16.1, RV1.2, TP9.1
TRIM_LO: R25.1, RV1.1
VG: D5.2 (A), R13.1, R18.1, R28.1, R42.1, TP23.1, U4.5 (OUT)
VIN: C1.1, C17.1, D1.1 (K), J1.2, Q1.3 (S), Q7.3 (S), R1.1, R14.1, R36.1, R41.1, TP1.1, U1.2 (A), U1.3 (VSNS)
VOUT: C6.1, C7.1, C8.1, C15.1, C16.1, D2.1 (K), D4.1 (K), D7.1 (K), D11.2 (A), J2.2, J3.2, J4.2, J5.2, J6.2, J7.2, Q2.3 (S), Q8.3 (S), R6.1, R10.1, R26.1, R44.1, TP3.1, U1.9 (OUT)
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
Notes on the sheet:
INPUT
XT60 from the supply (fuse it in the supply lead). TVS D1 and bulk C17.
White LED D8 = supply present.
IDEAL DIODE + SOFT START (U1 LM74800)
Q1||Q7 block regen into the supply. Q2||Q8 ramp the output at about 140 V/s (C4, C5, C13, C14 on CDVDT through R5). D11 clamps HGATE to VOUT + 12 V. SW1 = output on/off. UVLO ~13.5 V (R1/R2), OV ~57 V
(R3/R4).
OUTPUT BUS
Four 470 uF 100 V bulk capacitors, ceramic C6 and TVS D2. Five XT30 outputs, 15 A each: 1-3 arm, 4 gripper, 5 spare.
11.6 V CONTROL RAIL
Made from VOUT, so it runs while the arm back-drives the bus. CJ431 (U2) sets Q4's base; D12 clamps it under 17 V; D10
guards Q4's base-emitter. Green LED D3 = output live.
BRAKE COMPARATOR (U3A)
Brakes when VOUT - VIN > 0.667 x V(TRIM) - 0.14 V. RV1 sets +3.0 to +7.5 V (clockwise raises it). R13 adds about 2.3 V of hysteresis.
BRAKE DRIVER + MOSFETS
U4 (UCC27517) drives Q3||Q9 into the external resistor on J5 (2 ohm 200 W at 36 V, Q136 fuse in series). J11 = the resistor's thermal switch: open disables the brake. D4/D7 catch the resistor's kick.
BRAKE INTERLOCK
Q10/Q11 hold CMP_OUT low while the ideal diode conducts (DGATE above VIN).
THERM OPEN LED
Yellow D9 lights when the J11 loop is open.
RED BRAKE LED
U3B keeps red D6 lit for at least 0.3 s after any brake pulse (C12, R21).
MICROCONTROLLER HEADER
J12: 1 GND, 2 BUS_ADC (VOUT x 0.053), 3 BRK_FLAG (open drain, low while braking).
TEST POINTS, MOUNTING, FIDUCIALS
